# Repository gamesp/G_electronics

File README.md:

## Pi GAMESP Robot Electronics

## Catalog

- Esquematic and PCB (by [Xdesig][XDE01])

- Gerber 274 machines compatible.

- STL for slicer

- Images mounting Process and connections

- 3d sim (SketchUp, Private use)

## NodeMCU

- devkit-v1.0 [NodeMCU]

- NodeMCU License [NodeMCU_LIC]

## License

Every content in this repo, otherwise specified under subdirectories, is
licensed under [Creative Commons BY-SA](LICENSE).

[XDE01]: https://twitter.com/xdesig

[NodeMCU_LIC]: https://github.com/nodemcu/nodemcu-devkit-v1.0/blob/master/LICENSE
[NodeMCU]: https://github.com/nodemcu/nodemcu-devkit-v1.0

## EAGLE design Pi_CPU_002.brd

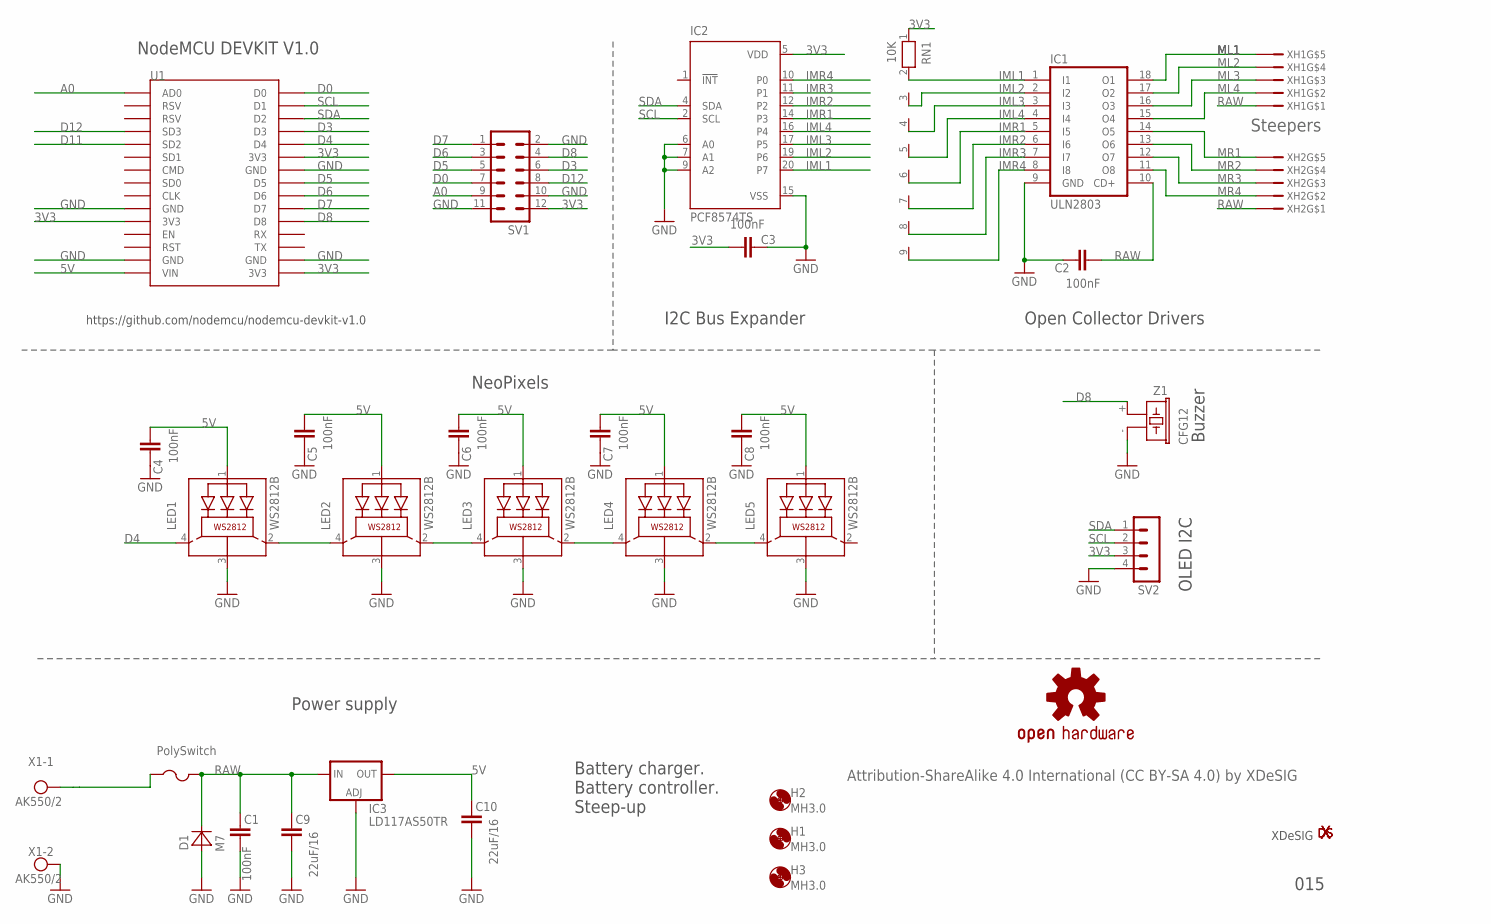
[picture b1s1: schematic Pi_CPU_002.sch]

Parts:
C1, C2, C3, C4, C5, C6, C7, C8: 100nF; C0603K
C9, C10: 22uF/16; C1206
D1: M7; SMA
F1: PolySwitch; R1206
H1, H2, H3: MH3.0; 3,0
IC1: ULN2803; DIL18
IC2: PCF8574TS; SSOP20
IC3: LD117AS50TR; SOT223
LED1, LED2, LED3, LED4, LED5: WS2812B; 5050-4
LOGO2: OSHW-LOGOS; OSHW-LOGO-S
RN1: 10K; RN-9
SV1: MA06-2
SV2: MA04-1
U1: ESP12E_DEVKIT
U$13: XDESIG_XDESIG21; XDESIG_XDESIG
X1: AK550/2
XDS1: XDESIG; XDESIG_CU_2
XH1, XH2: B5B-XH-A
Z1: CFG12; F/CM12P

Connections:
3V3: C3.2, IC2.5 (VDD), RN1.1, SV1.12, SV2.3, U1.3V3@0 (3V3), U1.3V3@1 (3V3), U1.3V3@2 (3V3)
5V: C4.2, C5.2, C6.2, C7.2, C8.2, C10.2, IC3.4 (OUT), LED1.1 (LEDVDD), LED2.1 (LEDVDD), LED3.1 (LEDVDD), LED4.1 (LEDVDD), LED5.1 (LEDVDD), U1.VIN
A0: SV1.9, U1.AD0
D0: SV1.7, U1.D0
D3: SV1.6, U1.D3
D4: LED1.4 (DI), U1.D4
D5: SV1.5, U1.D5
D6: SV1.3, U1.D6
D7: SV1.1, U1.D7
D8: SV1.4, U1.D8, Z1.+ (1)
D11: U1.SD2
D12: SV1.8, U1.SD3
GND: C1.1, C2.1, C3.1, C4.1, C5.1, C6.1, C7.1, C8.1, C9.1, C10.1, D1.A, IC1.9 (GND), IC2.6 (A0), IC2.7 (A1), IC2.9 (A2), IC2.15 (VSS), IC3.1 (ADJ), LED1.3 (GND), LED2.3 (GND), LED3.3 (GND), LED4.3 (GND), LED5.3 (GND), SV1.2, SV1.10, SV1.11, SV2.4, U1.GND@0 (GND), U1.GND@1 (GND), U1.GND@2 (GND), U1.GND@3 (GND), X1.2, Z1.- (2)
IML1: IC1.1 (I1), IC2.20 (P7), RN1.2
IML2: IC1.2 (I2), IC2.19 (P6), RN1.3
IML3: IC1.3 (I3), IC2.17 (P5), RN1.4
IML4: IC1.4 (I4), IC2.16 (P4), RN1.5
IMR1: IC1.5 (I5), IC2.14 (P3), RN1.6
IMR2: IC1.6 (I6), IC2.12 (P2), RN1.7
IMR3: IC1.7 (I7), IC2.11 (P1), RN1.8
IMR4: IC1.8 (I8), IC2.10 (P0), RN1.9
ML1: IC1.18 (O1), XH1.P$5
ML2: IC1.17 (O2), XH1.P$4
ML3: IC1.16 (O3), XH1.P$3
ML4: IC1.15 (O4), XH1.P$2
MR1: IC1.14 (O5), XH2.P$5
MR2: IC1.13 (O6), XH2.P$4
MR3: IC1.12 (O7), XH2.P$3
MR4: IC1.11 (O8), XH2.P$2
unnamed: F1.1, X1.1
unnamed: LED1.2 (DO), LED2.4 (DI)
unnamed: LED3.2 (DO), LED4.4 (DI)
unnamed: LED2.2 (DO), LED3.4 (DI)
unnamed: LED4.2 (DO), LED5.4 (DI)
RAW: C1.2, C2.2, C9.2, D1.C, F1.2, IC1.10 (CD+), IC3.3 (IN), XH1.P$1, XH2.P$1
SCL: IC2.2 (SCL), SV2.2, U1.D1
SDA: IC2.4 (SDA), SV2.1, U1.D2

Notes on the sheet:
Steepers
Attribution-ShareAlike 4.0 International (CC BY-SA 4.0) by XDeSIG
XDeSIG
015
OLED I2C
NeoPixels
NodeMCU DEVKIT V1.0
I2C Bus Expander
Open Collector Drivers
Buzzer
Power supply
Battery charger. Battery controller. Steep-up
https://github.com/nodemcu/nodemcu-devkit-v1.0

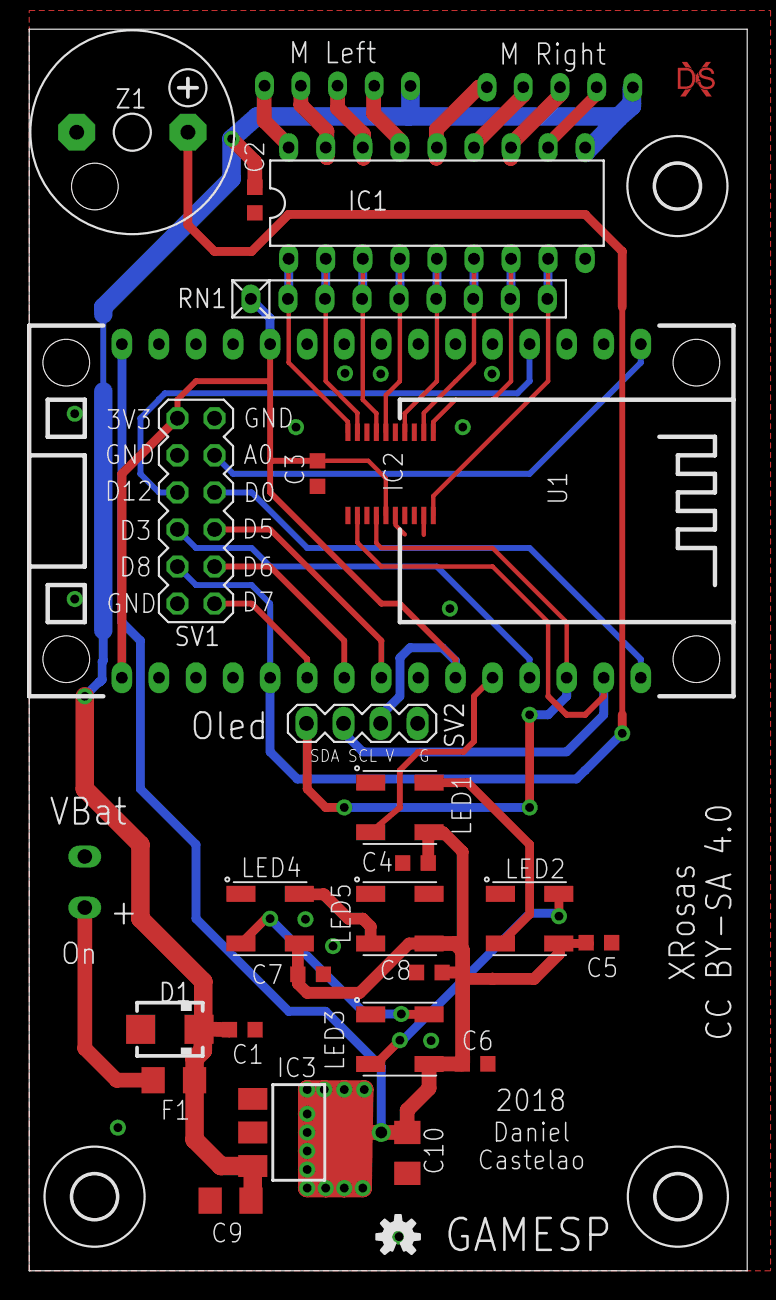
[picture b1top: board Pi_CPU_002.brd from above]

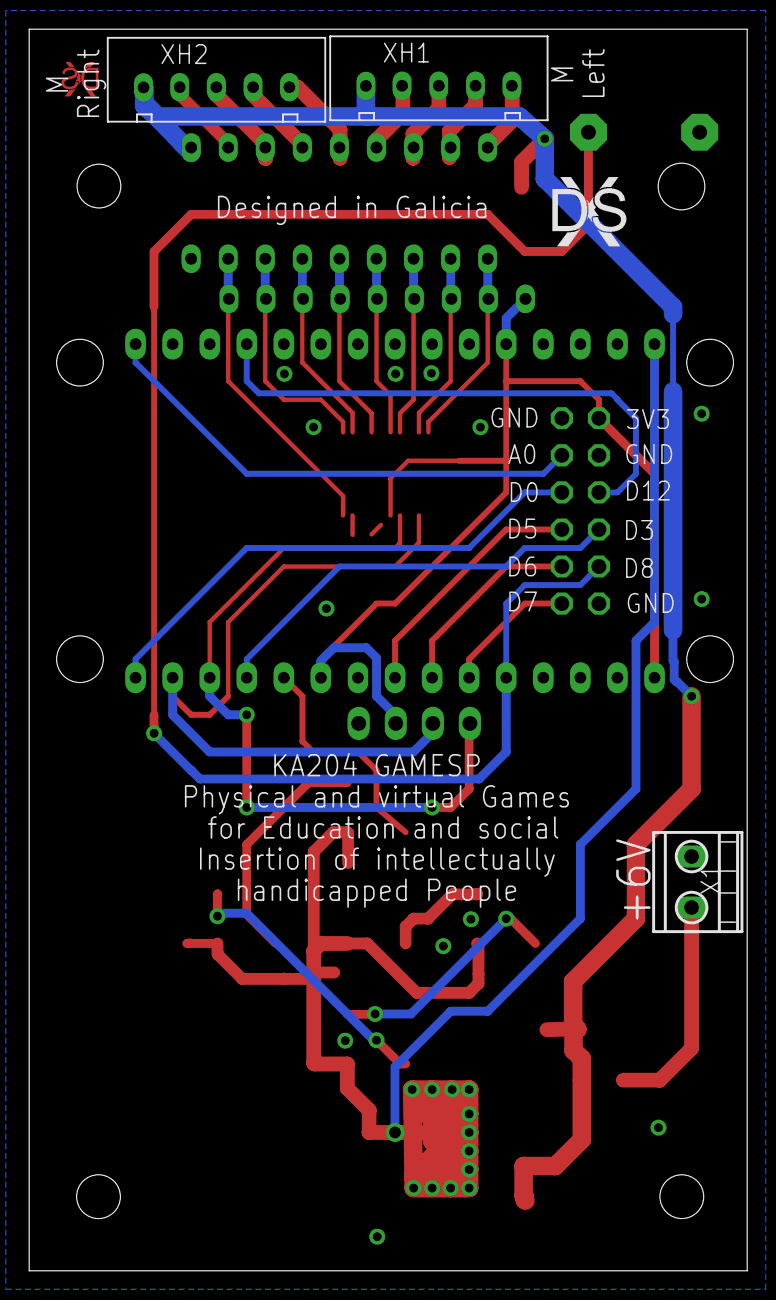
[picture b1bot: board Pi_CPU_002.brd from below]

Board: 2 copper layers, 49.2 x 85.1 mm, 34 parts (4 on the bottom side), 36 nets.

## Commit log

2018-05-04 Version 002

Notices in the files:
parts and their libraries:
SparkFun-Aesthetics: Licensing: CC v3.0 Share-Alike You are welcome to use this library for commercial purposes.
